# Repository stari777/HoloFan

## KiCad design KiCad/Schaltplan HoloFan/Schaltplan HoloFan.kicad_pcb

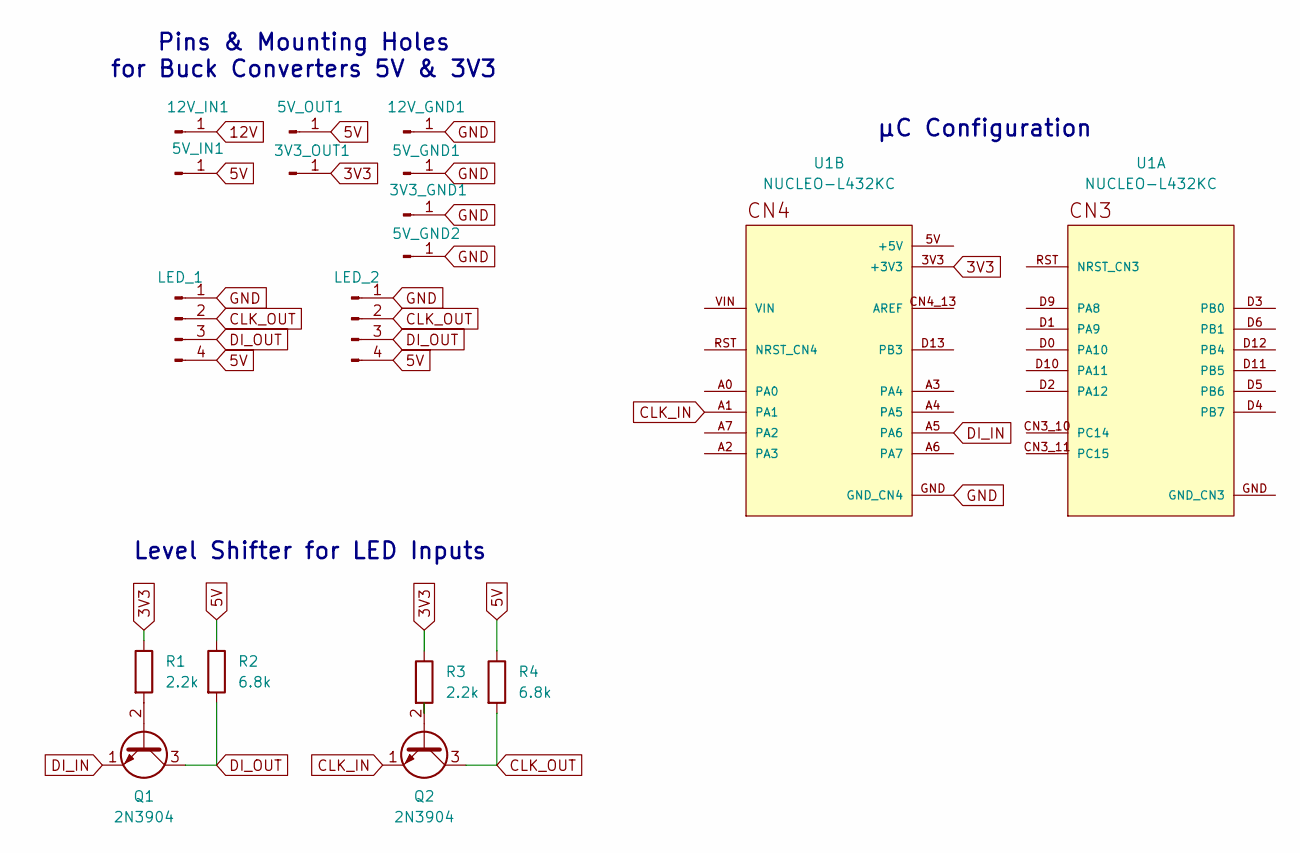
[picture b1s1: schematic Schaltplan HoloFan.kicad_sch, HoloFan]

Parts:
3V3_GND1, 3V3_OUT1, 5V_GND1, 5V_GND2, 5V_IN1, 5V_OUT1, 12V_GND1, 12V_IN1: Conn_01x01_Pin; PinHeader_1x01_P1.00mm_Vertical
LED_1, LED_2: Conn_01x04_Pin; APA102_Pads
Q1, Q2: 2N3904; TSOT-23
R1, R3: 2.2k; R_0603_1608Metric
R2, R4: 6.8k; R_0603_1608Metric
U1: NUCLEO-L432KC; MODULE_NUCLEO-L432KC; PARTREV N/A

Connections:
3V3: 3V3_OUT1.1, R1.1, R3.1, U1.3V3 (+3V3)
5V: 5V_IN1.1, 5V_OUT1.1, LED_1.4, LED_2.4, R2.1, R4.1
12V: 12V_IN1.1
CLK_IN: Q2.1 (E), U1.A1
CLK_OUT: LED_1.2, LED_2.2, Q2.3 (C), R4.2
DI_IN: Q1.1 (E), U1.A5 (PA6)
DI_OUT: LED_1.3, LED_2.3, Q1.3 (C), R2.2
GND: 3V3_GND1.1, 5V_GND1.1, 5V_GND2.1, 12V_GND1.1, LED_1.1, LED_2.1, U1.GND (GND_CN4)
unnamed: Q1.2 (B), R1.2
unnamed: Q2.2 (B), R3.2

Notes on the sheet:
µC Configuration
Pins & Mounting Holes for Buck Converters 5V & 3V3
Level Shifter for LED Inputs

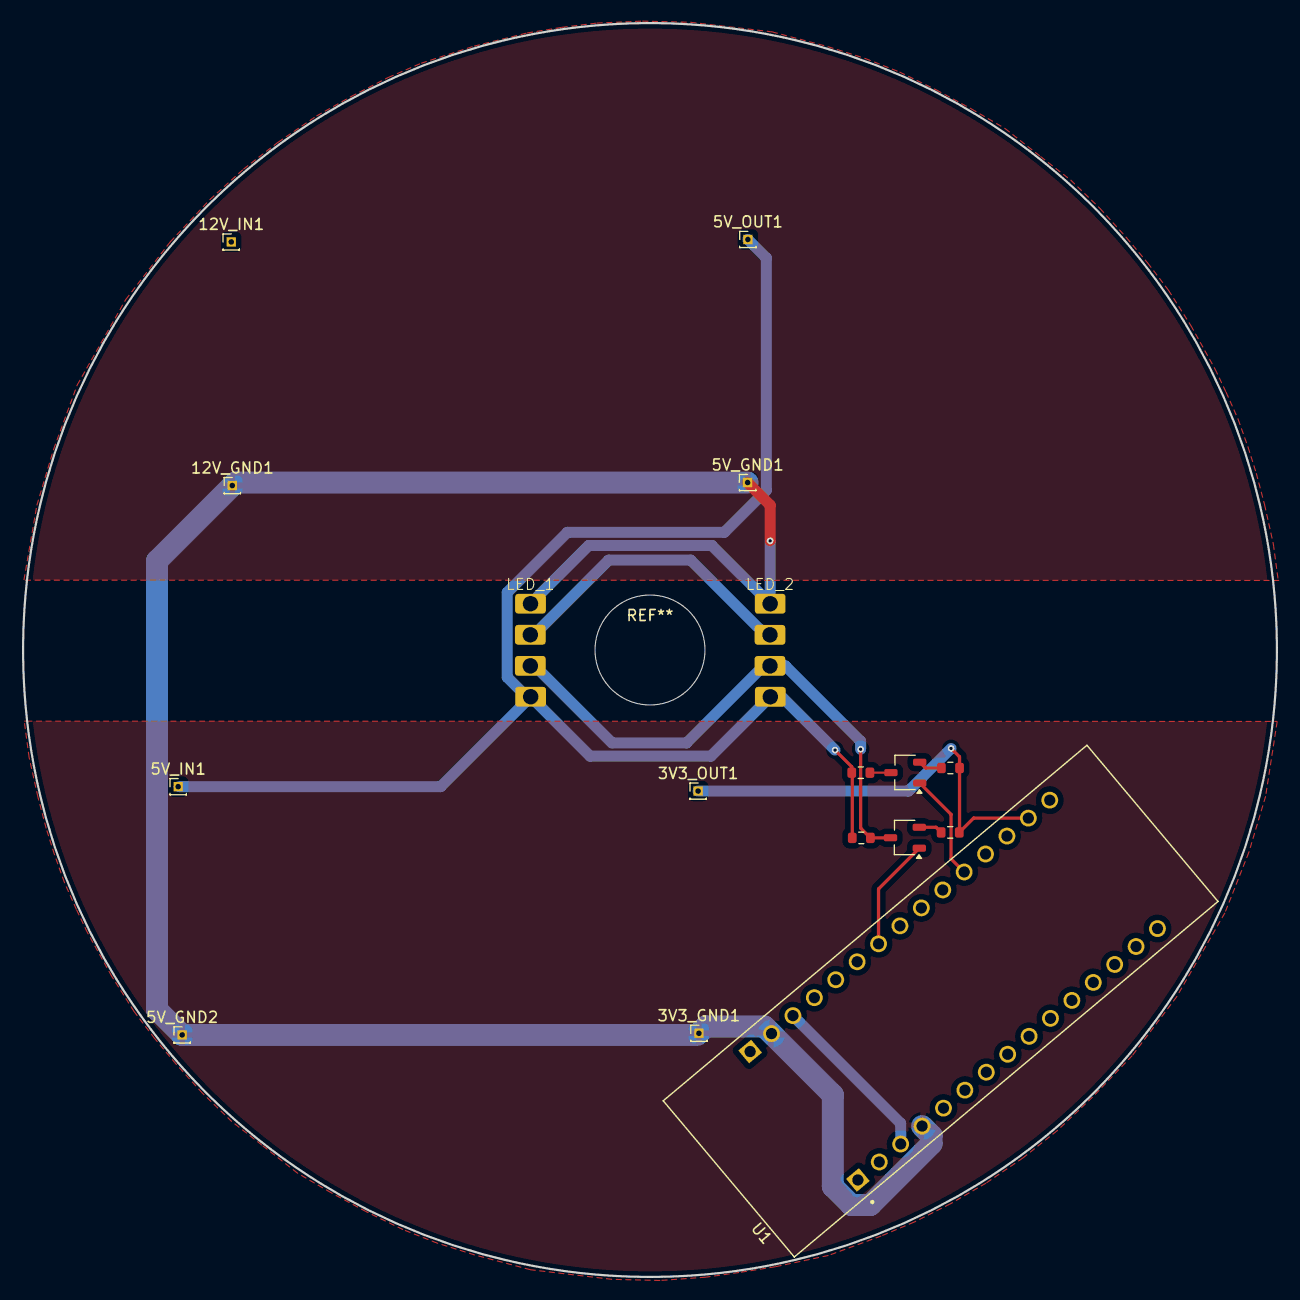
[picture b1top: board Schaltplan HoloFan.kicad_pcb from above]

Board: 2 copper layers, 114.0 x 114.0 mm, 17 parts (0 on the bottom side), 9 nets.

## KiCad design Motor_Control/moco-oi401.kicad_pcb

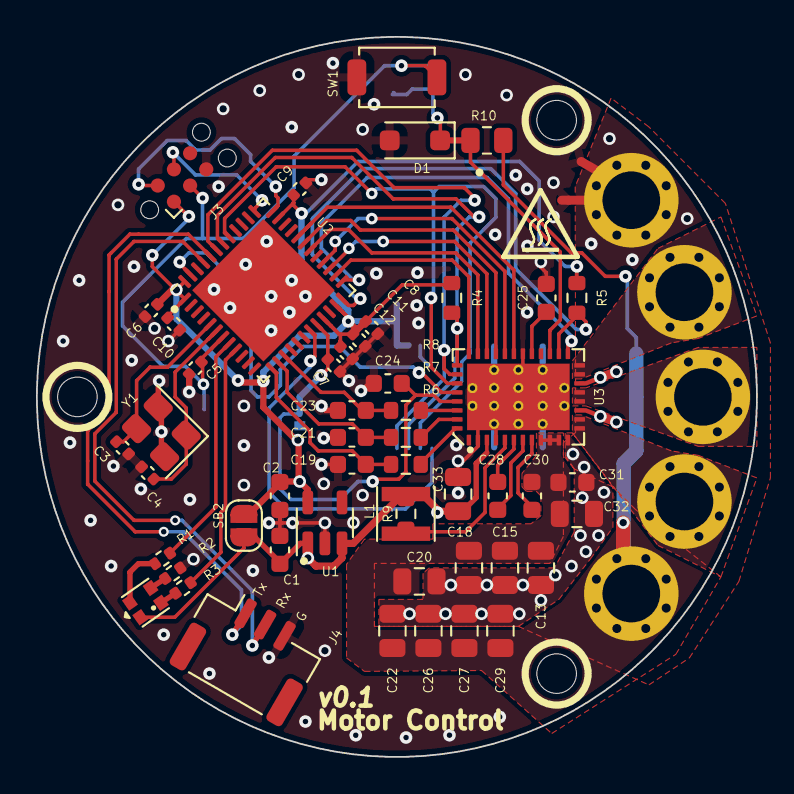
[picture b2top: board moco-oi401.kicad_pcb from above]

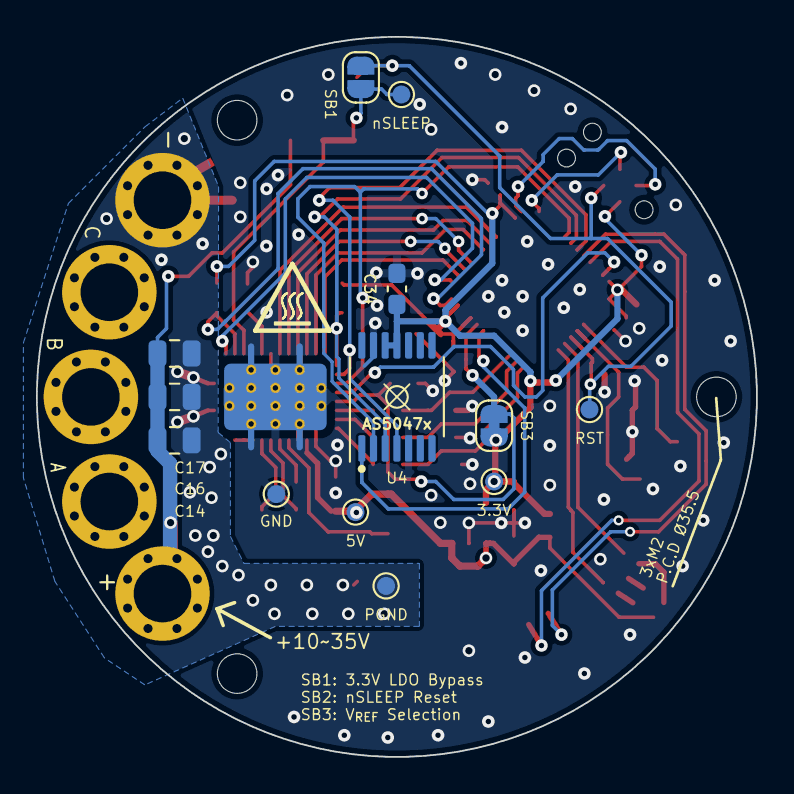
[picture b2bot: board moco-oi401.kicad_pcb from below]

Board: 2 copper layers, 40.0 x 40.0 mm, 74 parts (13 on the bottom side), 46 nets.

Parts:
C1, C2: 1uF; C_0603_1608Metric
C3, C4: 12pF; C_0402_1005Metric
C5, C6, C7, C8, C9, C10: 100nF; C_0402_1005Metric
C11: 10nF; C_0402_1005Metric
C12: 1uF; C_0402_1005Metric
C13, C14, C15, C16, C17, C18, C20, C22, C26, C27, C29, C32: 10uF/50V; C_0805_2012Metric
C19, C21, C23: 22pF; C_0603_1608Metric
C24: 100nF/6.3V; C_0603_1608Metric
C25: 1uF/6.3V; C_0603_1608Metric
C28: 47nF/50V; C_0603_1608Metric
C30: 1uF/16V; C_0603_1608Metric
C31: 100nF/50V; C_0603_1608Metric
C33: 22uF/16V; C_0805_2012Metric
C34: 100nF; C_0603_1608Metric_Pad1.08x0.95mm_HandSolder
D1: BZT52Bxx; D_SOD-123F
H1, H2, H3: MountingHole; MountingHole_2.2mm_M2_ISO14580
J1: V+; wire_3.2mm
J2: V-; wire_3.2mm
J3: Conn_ARM_SWD_TagConnect_TC2030-NL; Tag-Connect_TC2030-IDC-NL_2x03_P1.27mm_Vertical
J4: Serial; JST_GH_SM03B-GHS-TB_1x03-1MP_P1.25mm_Horizontal
J6: A; wire_3.2mm
J7: B; wire_3.2mm
J8: C; wire_3.2mm
L1: 47uH; L_Taiyo-Yuden_MD-3030
LD1: LED_BAGR; RGB LED 1.6x1.6mm
NT1, NT2: NetTie_2; NetTie-2_SMD_Pad0.5mm
R1, R2, R3: 1k; R_0402_1005Metric
R4, R5: 5.1k; R_0603_1608Metric
R6, R7, R8: 330R; R_0603_1608Metric
R9: 22R; R_0603_1608Metric
R10: 22k; R_0805_2012Metric
SB1, SB2: SolderJumper_2_Open; SolderJumper-2_P1.3mm_Open_RoundedPad1.0x1.5mm
SB3: SolderJumper_2_Bridged; SolderJumper-2_P1.3mm_Bridged_RoundedPad1.0x1.5mm
SW1: RESET; SW_SPST_TS-1088-xR020
TP1: GND; TestPoint_Pad_D1.0mm
TP2: ~{RESET}; TestPoint_Pad_D1.0mm
TP3: V_{CC}; TestPoint_Pad_D1.0mm
TP4: PGND; TestPoint_Pad_D1.0mm
TP5: V_{BK}; TestPoint_Pad_D1.0mm
TP6: nSLEEP; TestPoint_Pad_D1.0mm
U1: RT9013-33GB; SOT-23-5
U2: STM32G431CBUx; QFN-48-1EP_7x7mm_P0.5mm_EP5.6x5.6mm
U3: DRV8316CR; VQFN-40_RGF_5x7mm_0.5mm_pitch_thermalpad
U4: AS5047x; TSSOP-14_4.4x5mm_P0.65mm
Y1: 16MHz; Crystal_SMD_3225-4Pin_3.2x2.5mm

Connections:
+3.3V: C2.1, C6.1, C8.1, C9.1, C10.1, C11.1, C12.1, C34.2, J3.1 (VCC), R4.1, R5.1, SB2.2 (B), SB3.2 (B), TP3.1, U1.5 (VOUT), U2.1 (VBAT), U2.21 (VDDA), U2.23 (VDD), U2.35 (VDD), U2.48 (VDD), U4.11 (VDD), U4.12 (VDD3V3)
+5V: C1.1, C33.2, L1.2, LD1.2 (A), R9.2, SB2.1 (A), TP5.1, U1.1 (VIN), U1.3 (EN), U3.3 (FB_BK)
/ Rotary Sensor/MISO: R4.2, U2.42 (PB4), U3.33 (SDO), U4.3 (MISO)
/ Rotary Sensor/MOSI: U2.43 (PB5), U3.34 (SDI), U4.4 (MOSI)
/ Rotary Sensor/SCLK: U2.41 (PB3), U3.35 (SCLK), U4.2 (CLK)
/ Rotary Sensor/~CS: U2.19 (PB2), U4.1 (~CS)
/Driver/AVDD: C25.2, U3.25 (AVDD)
/Driver/DRVOFF: U2.25 (PB12), U3.21 (DRVOFF)
/Driver/INHA: U2.32 (PA10), U3.27 (INHA)
/Driver/INHB: U2.31 (PA9), U3.29 (INHB)
/Driver/INHC: U2.30 (PA8), U3.31 (INHC)
/Driver/INLA: U2.28 (PB15), U3.28 (INLA)
/Driver/INLB: U2.27 (PB14), U3.30 (INLB)
/Driver/INLC: U2.26 (PB13), U3.32 (INLC)
/Driver/OUTA: J6.1, U3.13 (OUTA), U3.14 (OUTA)
/Driver/OUTB: J7.1, U3.16 (OUTB), U3.17 (OUTB)
/Driver/OUTC: J8.1, U3.19 (OUTC), U3.20 (OUTC)
/Driver/SOA: C19.1, R6.1, U2.13 (PA5)
/Driver/SOB: C21.1, R7.1, U2.14 (PA6)
/Driver/SOC: C23.1, R8.1, U2.15 (PA7)
/Driver/V_{REF}: C7.1, C24.1, SB3.1 (A), U2.20 (VREF+), U3.37 (VREF/LILM)
/Driver/~CS: U2.47 (PB9), U3.36 (nSCS)
/Driver/~FAULT: R5.2, U2.24 (PB11), U3.22 (nFAULT)
/Driver/~SLEEP: D1.1 (K), R10.2, SB1.1 (A), TP6.1, U3.23 (nSLEEP)
/MCU/OSC_IN: C3.2, U2.5 (PF0), Y1.3
/MCU/OSC_OUT: C4.2, U2.6 (PF1), Y1.1
/SWCLK: J3.4 (SWCLK), U2.37 (PA14)
/SWDIO: J3.2 (SWDIO), U2.36 (PA13)
/UART1_RX: J4.2, U2.45 (PB7)
/UART1_TX: J4.1, U2.44 (PB6)
/USER_LED1: R1.2, U2.8 (PA0)
/USER_LED2: R3.2, U2.9 (PA1)
/~RESET: C5.1, J3.3 (~RESET), SB1.2 (B), SW1.2, TP2.1, U2.7 (PG10)
GND: C1.2, C2.2, C3.1, C4.1, C5.2, C6.2, C7.2, C8.2, C9.2, C10.2, C11.2, C12.2, C19.2, C21.2, C23.2, C24.2, C25.1, C33.1, C34.1, D1.2 (A), J3.5 (GND), J4.3, NT1.2, NT2.2, R2.2, SW1.1, TP1.1, U1.2 (GND), U2.49 (VSS), U3.2 (AGND), U3.4 (GND_BK), U3.26 (AGND), U3.41 (EP), U4.5 (TST), U4.13 (GND), Y1.2, Y1.4
GNDPWR: C13.2, C14.2, C15.2, C16.2, C17.2, C18.2, C20.2, C22.2, C26.2, C27.2, C29.2, C31.1, C32.1, J2.1, NT1.1, NT2.1, TP4.1, U3.12 (PGND), U3.15 (PGND), U3.18 (PGND)
unnamed: LD1.1 (BK), R3.1
unnamed: LD1.3 (GK), R2.1
unnamed: LD1.4 (RK), R1.1
unnamed: C30.1, U3.8 (CP)
unnamed: C28.2, U3.7 (CPH)
unnamed: C28.1, U3.6 (CPL)
unnamed: R6.2, U3.40 (SOA)
unnamed: R7.2, U3.39 (SOB)
unnamed: R8.2, U3.38 (SOC)
unnamed: L1.1, R9.1, U3.5 (SW_BK)
Vdrive: C13.1, C14.1, C15.1, C16.1, C17.1, C18.1, C20.1, C22.1, C26.1, C27.1, C29.1, C30.2, C31.2, C32.2, J1.1, R10.1, U3.9 (VM), U3.10 (VM), U3.11 (VM)

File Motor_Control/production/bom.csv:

Designator,Footprint,Quantity,Value,LCSC Part #
"C1, C2",0603,2,1uF,C15849
"C10, C5, C6, C7, C8, C9",0402,6,100nF,C1525
C11,0402,1,10nF,C15195
C12,0402,1,1uF,C52923
"C13, C15, C18, C20, C22, C26, C27, C29, C32",0805,9,10uF/50V,C440198
"C19, C21, C23",0603,3,22pF,C1653
C24,0603,1,100nF/6.3V,C14663
C25,0603,1,1uF/6.3V,C15849
C28,0603,1,47nF/50V,C1622
"C3, C4",0402,2,12pF,C1547
C30,0603,1,1uF/16V,C15849
C31,0603,1,100nF/50V,C14663
C33,0805,1,22uF/16V,C45783
D1,D_SOD-123F,1,BZT52Bxx,C19077392
J4,JST_GH_SM03B-GHS-TB_1x03-1MP_P1.25mm_Horizontal,1,Serial,C514175
L1,L_Taiyo-Yuden_MD-3030,1,47uH,C135243
LD1,RGB LED 1.6x1.6mm,1,LED_BAGR,C375569
"R1, R2, R3",0402,3,1k,C25104
R10,0805,1,22k,C17560
"R4, R5",0603,2,5.1k,C23186
"R6, R7, R8",0603,3,330R,C23138
"SB1, SB2",SolderJumper-2_P1.3mm_Open_RoundedPad1.0x1.5mm,2,SolderJumper_2_Open,
SB3,SolderJumper-2_P1.3mm_Bridged_RoundedPad1.0x1.5mm,1,SolderJumper_2_Bridged,
SW1,SW_SPST_TS-1088-xR020,1,RESET,C720477
TP1,TestPoint_Pad_D1.0mm,1,GND,
TP2,TestPoint_Pad_D1.0mm,1,~{RESET},
TP3,TestPoint_Pad_D1.0mm,1,V_{CC},
TP4,TestPoint_Pad_D1.0mm,1,PGND,
TP5,TestPoint_Pad_D1.0mm,1,V_{BK},
TP6,TestPoint_Pad_D1.0mm,1,nSLEEP,
U2,QFN-48-1EP_7x7mm_P0.5mm_EP5.6x5.6mm,1,STM32G431CBUx,C529356
U3,VQFN-40_RGF_5x7mm_0.5mm_pitch_thermalpad,1,DRV8316CR,C5447274
Y1,Crystal_SMD_3225-4Pin_3.2x2.5mm,1,16MHz,C13738

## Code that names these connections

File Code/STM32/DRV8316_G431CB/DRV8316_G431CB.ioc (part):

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Mcu.Name=STM32G431C(6-8-B)Ux
Mcu.Package=UFQFPN48
Mcu.UserName=STM32G431CBUx
PA10.Signal=S_TIM1_CH3
PA13.Mode=Serial_Wire
PA13.Signal=SYS_JTMS-SWDIO
PA14.Mode=Serial_Wire
PA14.Signal=SYS_JTCK-SWCLK
PA5.Signal=ADC2_IN13
PA6.Mode=IN3-Differential
PA6.Signal=ADC2_IN3
PA7.Mode=IN3-Differential
PA7.Signal=ADC2_IN4
PA8.Signal=S_TIM1_CH1
PA9.Signal=S_TIM1_CH2
PB12.GPIOParameters=GPIO_PuPd
PB12.GPIO_PuPd=GPIO_PULLDOWN
PB12.Signal=GPIO_Output
PB13.Signal=TIM1_CH1N
PB14.Signal=TIM1_CH2N
PB15.Signal=TIM1_CH3N
PB3.Mode=Simplex_Bidirectional_Master
PB3.Signal=SPI1_SCK
PB4.Signal=SPI1_MISO
PB5.Mode=Simplex_Bidirectional_Master
PB5.Signal=SPI1_MOSI
PB6.Mode=Asynchronous
PB6.Signal=USART1_TX
PB7.Mode=Asynchronous
PB7.Signal=USART1_RX
PB9.GPIOParameters=GPIO_Speed,GPIO_PuPd
PB9.GPIO_PuPd=GPIO_PULLDOWN
PB9.GPIO_Speed=GPIO_SPEED_FREQ_MEDIUM
PB9.Signal=GPIO_Output
PF0-OSC_IN.Mode=HSE-External-Oscillator
PF0-OSC_IN.Signal=RCC_OSC_IN
PF1-OSC_OUT.Mode=HSE-External-Oscillator
PF1-OSC_OUT.Signal=RCC_OSC_OUT
RCC.HSE_VALUE=16000000
RCC.SYSCLKFreq_VALUE=64000000
RCC.SYSCLKSource=RCC_SYSCLKSOURCE_PLLCLK
board=custom

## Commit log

2025-10-16 Ignoriert unnötige Daten
2025-10-16 Erste LED-Ansteuerung
2025-11-06 Init Projects
2025-11-06 Old Push deleted
2025-11-06 Deleted needless files
2025-11-13 LED-Ansteuerng nach Bilddaten
2025-11-19 Small Changes
2025-11-19 Snake Animation
2025-11-20 Snake 2 Bild
2025-12-03 Python GUI
2025-12-03 CoordtoPolar
2025-12-03 Python GUI Darkmode Update
2025-12-04 LED-Ansteuerung Debug Version
2026-01-08 check-in of Motor-Control prototyp design files (Kicad)
2026-02-12 Moved Repository
2026-02-12 DRV8316 Motor Treiber SPI
2026-02-12 Removed duplicate root folders
2026-02-25 LED-Ansteuerung fertig
2026-03-09 Python Programm Update + Timer Interrupt
2026-04-03 Finishing of HoloFan Project
2026-04-04 PCB Layout Finishing

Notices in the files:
Motor_Control/moco-oi401.kicad_pcb:
Open source hardware, CERN-OHL-P v2
